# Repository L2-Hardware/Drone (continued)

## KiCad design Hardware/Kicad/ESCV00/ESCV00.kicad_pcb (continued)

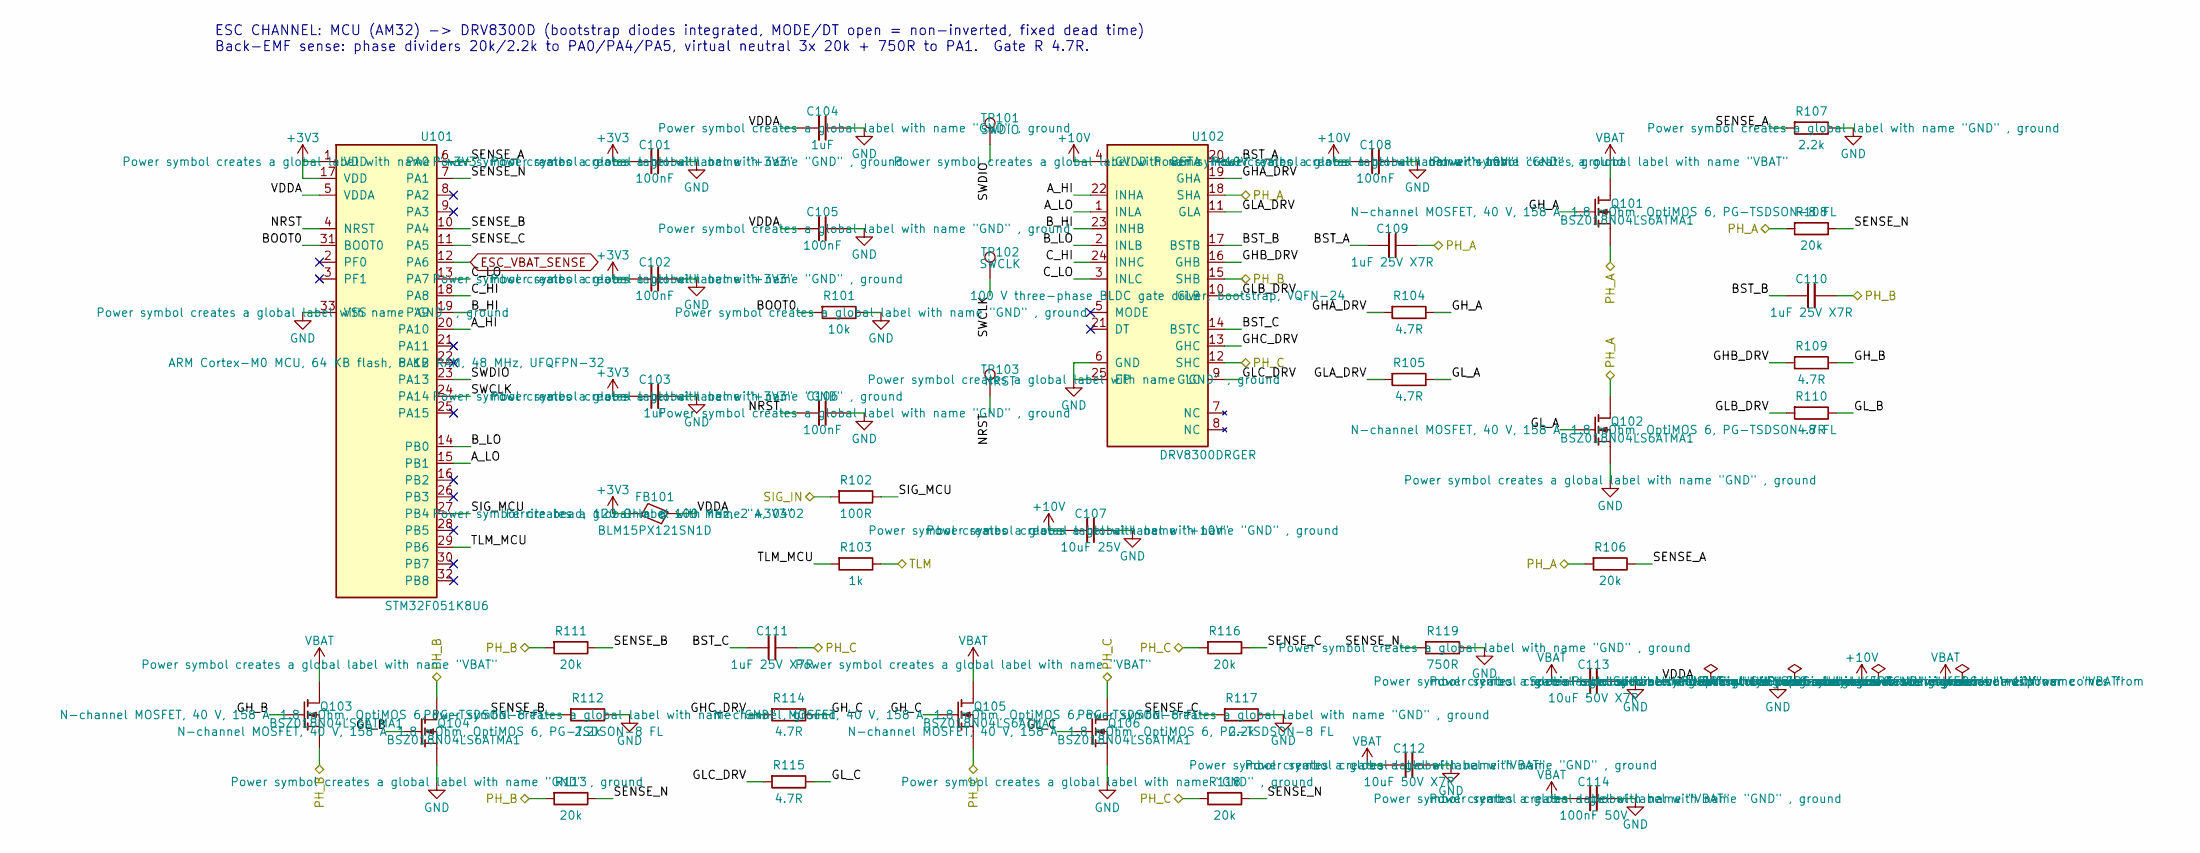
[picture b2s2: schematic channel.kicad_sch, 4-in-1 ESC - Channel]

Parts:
C101, C102, C105, C106, C108: 100nF; C_0402_1005Metric
C103, C104: 1uF; C_0402_1005Metric
C107: 10uF 25V; C_0805_2012Metric
C109, C110, C111: 1uF 25V X7R; C_0603_1608Metric
C112, C113: 10uF 50V X7R; C_1206_3216Metric
C114: 100nF 50V; C_0603_1608Metric
FB101: BLM15PX121SN1D
Q101, Q102, Q103, Q104, Q105, Q106: BSZ018N04LS6ATMA1
R101: 10k; R_0402_1005Metric
R102: 100R; R_0402_1005Metric
R103: 1k; R_0402_1005Metric
R104, R105, R109, R110, R114, R115: 4.7R; R_0402_1005Metric
R106, R108, R111, R113, R116, R118: 20k; R_0402_1005Metric
R107, R112, R117: 2.2k; R_0402_1005Metric
R119: 750R; R_0402_1005Metric
TP101: SWDIO; TestPoint_Pad_D1.0mm
TP102: SWCLK; TestPoint_Pad_D1.0mm
TP103: NRST; TestPoint_Pad_D1.0mm
U101: STM32F051K8U6
U102: DRV8300DRGER

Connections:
+3V3: C101.1, C102.1, C103.1, FB101.1, U101.1 (VDD), U101.17 (VDD); also elsewhere on the board
+10V: C107.1, C108.1, U102.4 (GVDD); also elsewhere on the board
/CH1/A_HI: U101.20 (PA10), U102.22 (INHA)
/CH1/A_LO: U101.15 (PB1), U102.1 (INLA)
/CH1/BOOT0: R101.1, U101.31 (BOOT0)
/CH1/BST_A: C109.1, U102.20 (BSTA)
/CH1/BST_B: C110.1, U102.17 (BSTB)
/CH1/BST_C: C111.1, U102.14 (BSTC)
/CH1/B_HI: U101.19 (PA9), U102.23 (INHB)
/CH1/B_LO: U101.14 (PB0), U102.2 (INLB)
/CH1/C_HI: U101.18 (PA8), U102.24 (INHC)
/CH1/C_LO: U101.13 (PA7), U102.3 (INLC)
/CH1/GHA_DRV: R104.1, U102.19 (GHA)
/CH1/GHB_DRV: R109.1, U102.16 (GHB)
/CH1/GHC_DRV: R114.1, U102.13 (GHC)
/CH1/GH_A: Q101.4 (G), R104.2
/CH1/GH_B: Q103.4 (G), R109.2
/CH1/GH_C: Q105.4 (G), R114.2
/CH1/GLA_DRV: R105.1, U102.11 (GLA)
/CH1/GLB_DRV: R110.1, U102.10 (GLB)
/CH1/GLC_DRV: R115.1, U102.9 (GLC)
/CH1/GL_A: Q102.4 (G), R105.2
/CH1/GL_B: Q104.4 (G), R110.2
/CH1/GL_C: Q106.4 (G), R115.2
/CH1/NRST: C106.1, TP103.1, U101.4 (NRST)
/CH1/SENSE_A: R106.2, R107.1, U101.6 (PA0)
/CH1/SENSE_B: R111.2, R112.1, U101.10 (PA4)
/CH1/SENSE_C: R116.2, R117.1, U101.11 (PA5)
/CH1/SENSE_N: R108.2, R113.2, R118.2, R119.1, U101.7 (PA1)
/CH1/SIG_MCU: R102.2, U101.27 (PB4)
/CH1/SWCLK: TP102.1, U101.24 (PA14)
/CH1/SWDIO: TP101.1, U101.23 (PA13)
/CH1/TLM_MCU: R103.1, U101.29 (PB6)
/CH1/VDDA: C104.1, C105.1, FB101.2, U101.5 (VDDA)
ESC_TLM: R103.2; also elsewhere on the board
ESC_VBAT_SENSE: U101.12 (PA6); also elsewhere on the board
GND: C101.2, C102.2, C103.2, C104.2, C105.2, C106.2, C107.2, C108.2, C112.2, C113.2, C114.2, Q102.1 (S), Q102.2 (S), Q102.3 (S), Q104.1 (S), Q104.2 (S), Q104.3 (S), Q106.1 (S), Q106.2 (S), Q106.3 (S), R101.2, R107.2, R112.2, R117.2, R119.2, U101.33 (VSS), U102.6 (GND), U102.25 (EP); also elsewhere on the board
M1_A: C109.2, Q101.1 (S), Q101.2 (S), Q101.3 (S), Q102.5 (D), R106.1, R108.1, U102.18 (SHA); also elsewhere on the board
M1_B: C110.2, Q103.1 (S), Q103.2 (S), Q103.3 (S), Q104.5 (D), R111.1, R113.1, U102.15 (SHB); also elsewhere on the board
M1_C: C111.2, Q105.1 (S), Q105.2 (S), Q105.3 (S), Q106.5 (D), R116.1, R118.1, U102.12 (SHC); also elsewhere on the board
MOTOR1: R102.1; also elsewhere on the board
VBAT: C112.1, C113.1, C114.1, Q101.5 (D), Q103.5 (D), Q105.5 (D); also elsewhere on the board

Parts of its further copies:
C201, C202, C205, C206, C208, C301, C302, C305, C306, C308, C401, C402, C405, C406, C408: 100nF; C_0402_1005Metric
C203, C204, C303, C304, C403, C404: 1uF; C_0402_1005Metric
C207, C307, C407: 10uF 25V; C_0805_2012Metric
C209, C210, C211, C309, C310, C311, C409, C410, C411: 1uF 25V X7R; C_0603_1608Metric
C212, C213, C312, C313, C412, C413: 10uF 50V X7R; C_1206_3216Metric
C214, C314, C414: 100nF 50V; C_0603_1608Metric
FB201, FB301, FB401: BLM15PX121SN1D
Q201, Q202, Q203, Q204, Q205, Q206, Q301, Q302, Q303, Q304, Q305, Q306, Q401, Q402, Q403, Q404, Q405, Q406: BSZ018N04LS6ATMA1
R201, R301, R401: 10k; R_0402_1005Metric
R202, R302, R402: 100R; R_0402_1005Metric
R203, R303, R403: 1k; R_0402_1005Metric
R204, R205, R209, R210, R214, R215, R304, R305, R309, R310, R314, R315, R404, R405, R409, R410, R414, R415: 4.7R; R_0402_1005Metric
R206, R208, R211, R213, R216, R218, R306, R308, R311, R313, R316, R318, R406, R408, R411, R413, R416, R418: 20k; R_0402_1005Metric
R207, R212, R217, R307, R312, R317, R407, R412, R417: 2.2k; R_0402_1005Metric
R219, R319, R419: 750R; R_0402_1005Metric
TP201, TP301, TP401: SWDIO; TestPoint_Pad_D1.0mm
TP202, TP302, TP402: SWCLK; TestPoint_Pad_D1.0mm
TP203, TP303, TP403: NRST; TestPoint_Pad_D1.0mm
U201, U301, U401: STM32F051K8U6
U202, U302, U402: DRV8300DRGER

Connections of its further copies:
+3V3: C201.1, C202.1, C203.1, C301.1, C302.1, C303.1, C401.1, C402.1, C403.1, FB201.1, FB301.1, FB401.1, U201.1 (VDD), U201.17 (VDD), U301.1 (VDD), U301.17 (VDD), U401.1 (VDD), U401.17 (VDD); also elsewhere on the board
+10V: C207.1, C208.1, C307.1, C308.1, C407.1, C408.1, U202.4 (GVDD), U302.4 (GVDD), U402.4 (GVDD); also elsewhere on the board
/CH2/A_HI: U201.20 (PA10), U202.22 (INHA)
/CH2/A_LO: U201.15 (PB1), U202.1 (INLA)
/CH2/BOOT0: R201.1, U201.31 (BOOT0)
/CH2/BST_A: C209.1, U202.20 (BSTA)
/CH2/BST_B: C210.1, U202.17 (BSTB)
/CH2/BST_C: C211.1, U202.14 (BSTC)
/CH2/B_HI: U201.19 (PA9), U202.23 (INHB)
/CH2/B_LO: U201.14 (PB0), U202.2 (INLB)
/CH2/C_HI: U201.18 (PA8), U202.24 (INHC)
/CH2/C_LO: U201.13 (PA7), U202.3 (INLC)
/CH2/GHA_DRV: R204.1, U202.19 (GHA)
/CH2/GHB_DRV: R209.1, U202.16 (GHB)
/CH2/GHC_DRV: R214.1, U202.13 (GHC)
/CH2/GH_A: Q201.4 (G), R204.2
/CH2/GH_B: Q203.4 (G), R209.2
/CH2/GH_C: Q205.4 (G), R214.2
/CH2/GLA_DRV: R205.1, U202.11 (GLA)
/CH2/GLB_DRV: R210.1, U202.10 (GLB)
/CH2/GLC_DRV: R215.1, U202.9 (GLC)
/CH2/GL_A: Q202.4 (G), R205.2
/CH2/GL_B: Q204.4 (G), R210.2
/CH2/GL_C: Q206.4 (G), R215.2
/CH2/NRST: C206.1, TP203.1, U201.4 (NRST)
/CH2/SENSE_A: R206.2, R207.1, U201.6 (PA0)
/CH2/SENSE_B: R211.2, R212.1, U201.10 (PA4)
/CH2/SENSE_C: R216.2, R217.1, U201.11 (PA5)
/CH2/SENSE_N: R208.2, R213.2, R218.2, R219.1, U201.7 (PA1)
/CH2/SIG_MCU: R202.2, U201.27 (PB4)
/CH2/SWCLK: TP202.1, U201.24 (PA14)
/CH2/SWDIO: TP201.1, U201.23 (PA13)
/CH2/TLM_MCU: R203.1, U201.29 (PB6)
/CH2/VDDA: C204.1, C205.1, FB201.2, U201.5 (VDDA)
/CH3/A_HI: U301.20 (PA10), U302.22 (INHA)
/CH3/A_LO: U301.15 (PB1), U302.1 (INLA)
/CH3/BOOT0: R301.1, U301.31 (BOOT0)
/CH3/BST_A: C309.1, U302.20 (BSTA)
/CH3/BST_B: C310.1, U302.17 (BSTB)
/CH3/BST_C: C311.1, U302.14 (BSTC)
/CH3/B_HI: U301.19 (PA9), U302.23 (INHB)
/CH3/B_LO: U301.14 (PB0), U302.2 (INLB)
/CH3/C_HI: U301.18 (PA8), U302.24 (INHC)
/CH3/C_LO: U301.13 (PA7), U302.3 (INLC)
/CH3/GHA_DRV: R304.1, U302.19 (GHA)
/CH3/GHB_DRV: R309.1, U302.16 (GHB)
/CH3/GHC_DRV: R314.1, U302.13 (GHC)
/CH3/GH_A: Q301.4 (G), R304.2
/CH3/GH_B: Q303.4 (G), R309.2
/CH3/GH_C: Q305.4 (G), R314.2
/CH3/GLA_DRV: R305.1, U302.11 (GLA)
/CH3/GLB_DRV: R310.1, U302.10 (GLB)
/CH3/GLC_DRV: R315.1, U302.9 (GLC)
/CH3/GL_A: Q302.4 (G), R305.2
/CH3/GL_B: Q304.4 (G), R310.2
/CH3/GL_C: Q306.4 (G), R315.2
/CH3/NRST: C306.1, TP303.1, U301.4 (NRST)
/CH3/SENSE_A: R306.2, R307.1, U301.6 (PA0)
/CH3/SENSE_B: R311.2, R312.1, U301.10 (PA4)
/CH3/SENSE_C: R316.2, R317.1, U301.11 (PA5)
/CH3/SENSE_N: R308.2, R313.2, R318.2, R319.1, U301.7 (PA1)
/CH3/SIG_MCU: R302.2, U301.27 (PB4)
/CH3/SWCLK: TP302.1, U301.24 (PA14)
/CH3/SWDIO: TP301.1, U301.23 (PA13)
/CH3/TLM_MCU: R303.1, U301.29 (PB6)
/CH3/VDDA: C304.1, C305.1, FB301.2, U301.5 (VDDA)
/CH4/A_HI: U401.20 (PA10), U402.22 (INHA)
/CH4/A_LO: U401.15 (PB1), U402.1 (INLA)
/CH4/BOOT0: R401.1, U401.31 (BOOT0)
/CH4/BST_A: C409.1, U402.20 (BSTA)
/CH4/BST_B: C410.1, U402.17 (BSTB)
/CH4/BST_C: C411.1, U402.14 (BSTC)
/CH4/B_HI: U401.19 (PA9), U402.23 (INHB)
/CH4/B_LO: U401.14 (PB0), U402.2 (INLB)
/CH4/C_HI: U401.18 (PA8), U402.24 (INHC)
/CH4/C_LO: U401.13 (PA7), U402.3 (INLC)
/CH4/GHA_DRV: R404.1, U402.19 (GHA)
/CH4/GHB_DRV: R409.1, U402.16 (GHB)
/CH4/GHC_DRV: R414.1, U402.13 (GHC)
/CH4/GH_A: Q401.4 (G), R404.2
/CH4/GH_B: Q403.4 (G), R409.2
/CH4/GH_C: Q405.4 (G), R414.2
/CH4/GLA_DRV: R405.1, U402.11 (GLA)
/CH4/GLB_DRV: R410.1, U402.10 (GLB)
/CH4/GLC_DRV: R415.1, U402.9 (GLC)
/CH4/GL_A: Q402.4 (G), R405.2
/CH4/GL_B: Q404.4 (G), R410.2
/CH4/GL_C: Q406.4 (G), R415.2
/CH4/NRST: C406.1, TP403.1, U401.4 (NRST)
/CH4/SENSE_A: R406.2, R407.1, U401.6 (PA0)
/CH4/SENSE_B: R411.2, R412.1, U401.10 (PA4)
/CH4/SENSE_C: R416.2, R417.1, U401.11 (PA5)
/CH4/SENSE_N: R408.2, R413.2, R418.2, R419.1, U401.7 (PA1)
/CH4/SIG_MCU: R402.2, U401.27 (PB4)
/CH4/SWCLK: TP402.1, U401.24 (PA14)
/CH4/SWDIO: TP401.1, U401.23 (PA13)
/CH4/TLM_MCU: R403.1, U401.29 (PB6)
/CH4/VDDA: C404.1, C405.1, FB401.2, U401.5 (VDDA)
ESC_TLM: R203.2, R303.2, R403.2; also elsewhere on the board
ESC_VBAT_SENSE: U201.12 (PA6), U301.12 (PA6), U401.12 (PA6); also elsewhere on the board
GND: C201.2, C202.2, C203.2, C204.2, C205.2, C206.2, C207.2, C208.2, C212.2, C213.2, C214.2, C301.2, C302.2, C303.2, C304.2, C305.2, C306.2, C307.2, C308.2, C312.2, C313.2, C314.2, C401.2, C402.2, C403.2, C404.2, C405.2, C406.2, C407.2, C408.2, C412.2, C413.2, C414.2, Q202.1 (S), Q202.2 (S), Q202.3 (S), Q204.1 (S), Q204.2 (S), Q204.3 (S), Q206.1 (S), Q206.2 (S), Q206.3 (S), Q302.1 (S), Q302.2 (S), Q302.3 (S), Q304.1 (S), Q304.2 (S), Q304.3 (S), Q306.1 (S), Q306.2 (S), Q306.3 (S), Q402.1 (S), Q402.2 (S), Q402.3 (S), Q404.1 (S), Q404.2 (S), Q404.3 (S), Q406.1 (S), Q406.2 (S), Q406.3 (S), R201.2, R207.2, R212.2, R217.2, R219.2, R301.2, R307.2, R312.2, R317.2, R319.2, R401.2, R407.2, R412.2, R417.2, R419.2, U201.33 (VSS), U202.6 (GND), U202.25 (EP), U301.33 (VSS), U302.6 (GND), U302.25 (EP), U401.33 (VSS), U402.6 (GND), U402.25 (EP); also elsewhere on the board
M2_A: C209.2, Q201.1 (S), Q201.2 (S), Q201.3 (S), Q202.5 (D), R206.1, R208.1, U202.18 (SHA); also elsewhere on the board
M2_B: C210.2, Q203.1 (S), Q203.2 (S), Q203.3 (S), Q204.5 (D), R211.1, R213.1, U202.15 (SHB); also elsewhere on the board
M2_C: C211.2, Q205.1 (S), Q205.2 (S), Q205.3 (S), Q206.5 (D), R216.1, R218.1, U202.12 (SHC); also elsewhere on the board
M3_A: C309.2, Q301.1 (S), Q301.2 (S), Q301.3 (S), Q302.5 (D), R306.1, R308.1, U302.18 (SHA); also elsewhere on the board
M3_B: C310.2, Q303.1 (S), Q303.2 (S), Q303.3 (S), Q304.5 (D), R311.1, R313.1, U302.15 (SHB); also elsewhere on the board
M3_C: C311.2, Q305.1 (S), Q305.2 (S), Q305.3 (S), Q306.5 (D), R316.1, R318.1, U302.12 (SHC); also elsewhere on the board
M4_A: C409.2, Q401.1 (S), Q401.2 (S), Q401.3 (S), Q402.5 (D), R406.1, R408.1, U402.18 (SHA); also elsewhere on the board
M4_B: C410.2, Q403.1 (S), Q403.2 (S), Q403.3 (S), Q404.5 (D), R411.1, R413.1, U402.15 (SHB); also elsewhere on the board
M4_C: C411.2, Q405.1 (S), Q405.2 (S), Q405.3 (S), Q406.5 (D), R416.1, R418.1, U402.12 (SHC); also elsewhere on the board
MOTOR2: R202.1; also elsewhere on the board
MOTOR3: R302.1; also elsewhere on the board
MOTOR4: R402.1; also elsewhere on the board
VBAT: C212.1, C213.1, C214.1, C312.1, C313.1, C314.1, C412.1, C413.1, C414.1, Q201.5 (D), Q203.5 (D), Q205.5 (D), Q301.5 (D), Q303.5 (D), Q305.5 (D), Q401.5 (D), Q403.5 (D), Q405.5 (D); also elsewhere on the board

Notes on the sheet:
ESC CHANNEL: MCU (AM32) -> DRV8300D (bootstrap diodes integrated, MODE/DT open = non-inverted, fixed dead time) Back-EMF sense: phase dividers 20k/2.2k to PA0/PA4/PA5, virtual neutral 3x 20k + 750R to PA1. Gate R 4.7R.

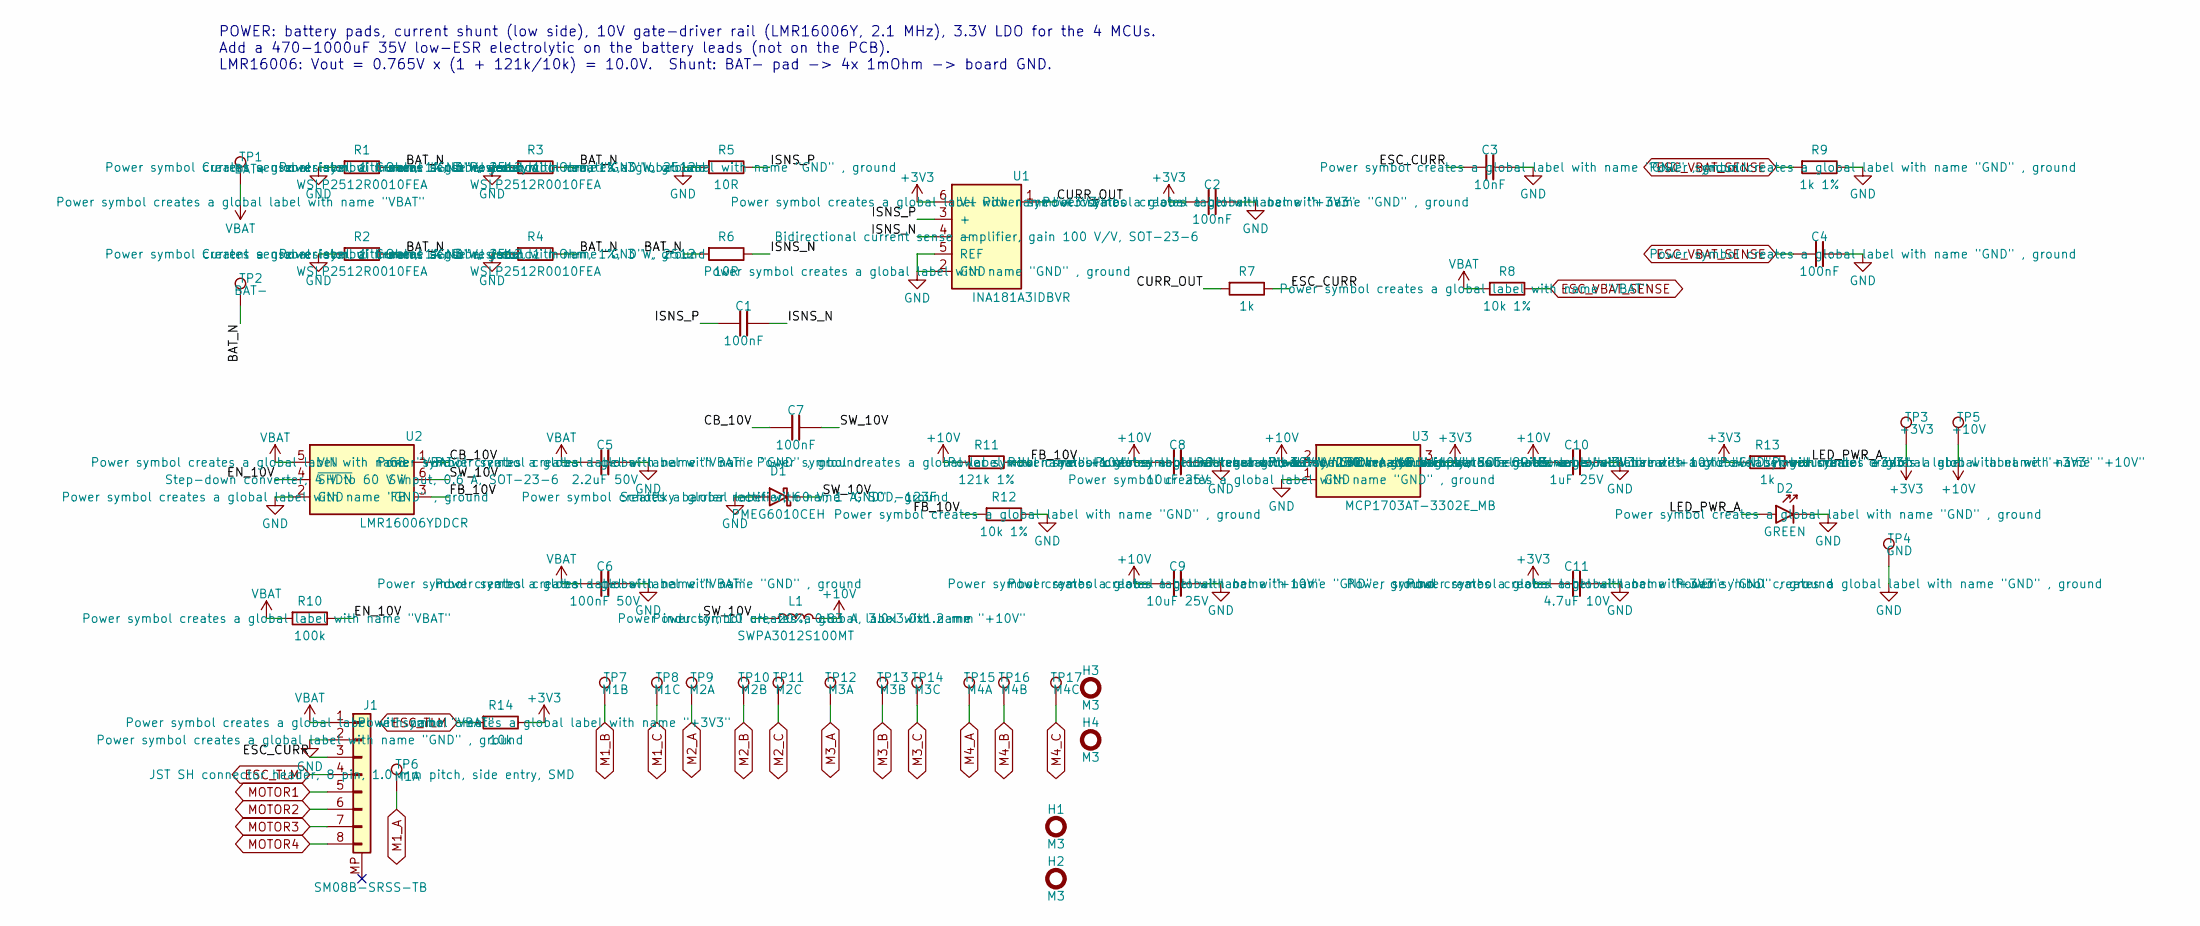
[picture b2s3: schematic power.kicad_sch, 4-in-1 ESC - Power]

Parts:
C1, C2, C4, C7: 100nF; C_0402_1005Metric
C3: 10nF; C_0402_1005Metric
C5: 2.2uF 50V; C_0805_2012Metric
C6: 100nF 50V; C_0603_1608Metric
C8, C9: 10uF 25V; C_0805_2012Metric
C10: 1uF 25V; C_0603_1608Metric
C11: 4.7uF 10V; C_0603_1608Metric
D1: PMEG6010CEH
D2: GREEN; LED_0603_1608Metric
H1, H2, H3, H4: M3; MountingHole_3.2mm_M3
J1: SM08B-SRSS-TB
L1: SWPA3012S100MT
R1, R2, R3, R4: WSLP2512R0010FEA
R5, R6: 10R; R_0402_1005Metric
R7, R13: 1k; R_0402_1005Metric
R8, R12: 10k 1%; R_0402_1005Metric
R9: 1k 1%; R_0402_1005Metric
R10: 100k; R_0402_1005Metric
R11: 121k 1%; R_0402_1005Metric
R14: 10k; R_0402_1005Metric
TP1: BAT+; SolderPad_5x8mm
TP2: BAT-; SolderPad_5x8mm
TP3: +3V3; TestPoint_Pad_D1.5mm
TP4: GND; TestPoint_Pad_D1.5mm
TP5: +10V; TestPoint_Pad_D1.5mm
TP6: M1A; SolderPad_3x5mm
TP7: M1B; SolderPad_3x5mm
TP8: M1C; SolderPad_3x5mm
TP9: M2A; SolderPad_3x5mm
TP10: M2B; SolderPad_3x5mm
TP11: M2C; SolderPad_3x5mm
TP12: M3A; SolderPad_3x5mm
TP13: M3B; SolderPad_3x5mm
TP14: M3C; SolderPad_3x5mm
TP15: M4A; SolderPad_3x5mm
TP16: M4B; SolderPad_3x5mm
TP17: M4C; SolderPad_3x5mm
U1: INA181A3IDBVR
U2: LMR16006YDDCR
U3: MCP1703AT-3302E_MB

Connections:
+3V3: C2.1, C11.1, R13.1, R14.2, TP3.1, U1.6 (V+), U3.3 (VO); also elsewhere on the board
+10V: C8.1, C9.1, C10.1, L1.2, R11.1, TP5.1, U3.2 (VI); also elsewhere on the board
/Power/BAT_N: R1.2, R2.2, R3.2, R4.2, R6.1, TP2.1
/Power/CB_10V: C7.1, U2.1 (CB)
/Power/CURR_OUT: R7.1, U1.1
/Power/EN_10V: R10.2, U2.4 (~SHDN)
/Power/ESC_CURR: C3.1, J1.3, R7.2
/Power/FB_10V: R11.2, R12.1, U2.3 (FB)
/Power/ISNS_N: C1.2, R6.2, U1.4 (-)
/Power/ISNS_P: C1.1, R5.2, U1.3 (+)
/Power/LED_PWR_A: D2.2 (A), R13.2
/Power/SW_10V: C7.2, D1.1 (K), L1.1, U2.6 (SW)
ESC_TLM: J1.4, R14.1; also elsewhere on the board
ESC_VBAT_SENSE: C4.1, R8.2, R9.1; also elsewhere on the board
GND: C2.2, C3.2, C4.2, C5.2, C6.2, C8.2, C9.2, C10.2, C11.2, D1.2 (A), D2.1 (K), J1.2, R1.1, R2.1, R3.1, R4.1, R5.1, R9.2, R12.2, TP4.1, U1.2 (GND), U1.5 (REF), U2.2 (GND), U3.1 (GND); also elsewhere on the board
M1_A: TP6.1; also elsewhere on the board
M1_B: TP7.1; also elsewhere on the board
M1_C: TP8.1; also elsewhere on the board
M2_A: TP9.1; also elsewhere on the board
M2_B: TP10.1; also elsewhere on the board
M2_C: TP11.1; also elsewhere on the board
M3_A: TP12.1; also elsewhere on the board
M3_B: TP13.1; also elsewhere on the board
M3_C: TP14.1; also elsewhere on the board
M4_A: TP15.1; also elsewhere on the board
M4_B: TP16.1; also elsewhere on the board
M4_C: TP17.1; also elsewhere on the board
MOTOR1: J1.5; also elsewhere on the board
MOTOR2: J1.6; also elsewhere on the board
MOTOR3: J1.7; also elsewhere on the board
MOTOR4: J1.8; also elsewhere on the board
VBAT: C5.1, C6.1, J1.1, R8.1, R10.1, TP1.1, U2.5 (VIN); also elsewhere on the board

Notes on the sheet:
POWER: battery pads, current shunt (low side), 10V gate-driver rail (LMR16006Y, 2.1 MHz), 3.3V LDO for the 4 MCUs. Add a 470-1000uF 35V low-ESR electrolytic on the battery leads (not on the PCB). LMR16006: Vout = 0.765V x (1 + 121k/10k) = 10.0V. Shunt: BAT- pad -> 4x 1mOhm -> board GND.

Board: 6 copper layers, 233 parts (0 on the bottom side), 160 nets, no tracks yet.

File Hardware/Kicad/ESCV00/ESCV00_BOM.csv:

"Qty","References","Value","Footprint","DNP"
"24","C1,C2,C4,C7,C101,C102,C105,C106,C108,C201,C202,C205,C206,C208,C301,C302,C305,C306,C308,C401,C402,C405,C406,C408","100nF","eCapacitor:C_0402_1005Metric",""
"1","C3","10nF","eCapacitor:C_0402_1005Metric",""
"1","C5","2.2uF 50V","eCapacitor:C_0805_2012Metric",""
"5","C6,C114,C214,C314,C414","100nF 50V","eCapacitor:C_0603_1608Metric",""
"6","C8,C9,C107,C207,C307,C407","10uF 25V","eCapacitor:C_0805_2012Metric",""
"1","C10","1uF 25V","eCapacitor:C_0603_1608Metric",""
"1","C11","4.7uF 10V","eCapacitor:C_0603_1608Metric",""
"8","C103,C104,C203,C204,C303,C304,C403,C404","1uF","eCapacitor:C_0402_1005Metric",""
"12","C109,C110,C111,C209,C210,C211,C309,C310,C311,C409,C410,C411","1uF 25V X7R","eCapacitor:C_0603_1608Metric",""
"8","C112,C113,C212,C213,C312,C313,C412,C413","10uF 50V X7R","eCapacitor:C_1206_3216Metric",""
"1","D1","PMEG6010CEH","eDiodes:PMEG6010CEH",""
"1","D2","GREEN","eLED:LED_0603_1608Metric",""
"4","FB101,FB201,FB301,FB401","BLM15PX121SN1D","eFerrite:BLM15PX121SN1D",""
"1","J1","SM08B-SRSS-TB","eConnector:SM08B-SRSS-TB",""
"1","L1","SWPA3012S100MT","eCoil:SWPA3012S100MT",""
"24","Q101,Q102,Q103,Q104,Q105,Q106,Q201,Q202,Q203,Q204,Q205,Q206,Q301,Q302,Q303,Q304,Q305,Q306,Q401,Q402,Q403,Q404,Q405,Q406","BSZ018N04LS6ATMA1","eTransistor:BSZ018N04LS6ATMA1",""
"4","R1,R2,R3,R4","WSLP2512R0010FEA","eResistor:WSLP2512R0010FEA",""
"2","R5,R6","10R","eResistor:R_0402_1005Metric",""
"6","R7,R13,R103,R203,R303,R403","1k","eResistor:R_0402_1005Metric",""
"2","R8,R12","10k 1%","eResistor:R_0402_1005Metric",""
"1","R9","1k 1%","eResistor:R_0402_1005Metric",""
"1","R10","100k","eResistor:R_0402_1005Metric",""
"1","R11","121k 1%","eResistor:R_0402_1005Metric",""
"5","R14,R101,R201,R301,R401","10k","eResistor:R_0402_1005Metric",""
"4","R102,R202,R302,R402","100R","eResistor:R_0402_1005Metric",""
"24","R104,R105,R109,R110,R114,R115,R204,R205,R209,R210,R214,R215,R304,R305,R309,R310,R314,R315,R404,R405,R409,R410,R414,R415","4.7R","eResistor:R_0402_1005Metric",""
"24","R106,R108,R111,R113,R116,R118,R206,R208,R211,R213,R216,R218,R306,R308,R311,R313,R316,R318,R406,R408,R411,R413,R416,R418","20k","eResistor:R_0402_1005Metric",""
"12","R107,R112,R117,R207,R212,R217,R307,R312,R317,R407,R412,R417","2.2k","eResistor:R_0402_1005Metric",""
"4","R119,R219,R319,R419","750R","eResistor:R_0402_1005Metric",""
"1","U1","INA181A3IDBVR","eAmplifier:INA181A3IDBVR",""
"1","U2","LMR16006YDDCR","eConverterDCDC:LMR16006YDDCR",""
"1","U3","MCP1703AT-3302E_MB","eLinearReg:MCP1703AT-3302E_MB",""
"4","U101,U201,U301,U401","STM32F051K8U6","eMCU:STM32F051K8U6",""
"4","U102,U202,U302,U402","DRV8300DRGER","eInterface:DRV8300DRGER",""

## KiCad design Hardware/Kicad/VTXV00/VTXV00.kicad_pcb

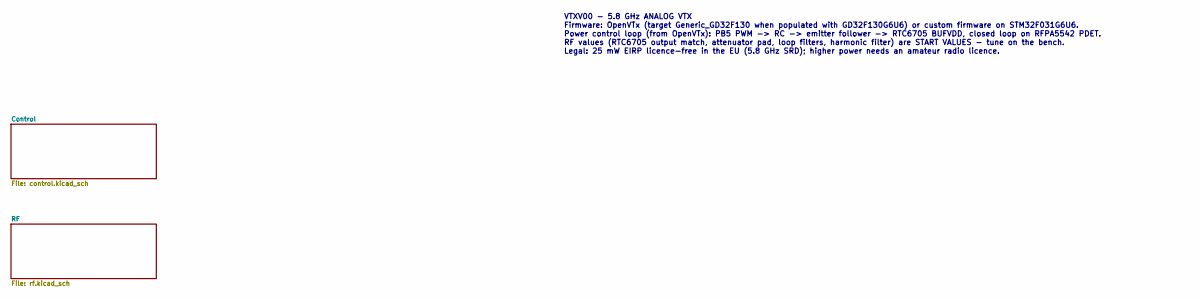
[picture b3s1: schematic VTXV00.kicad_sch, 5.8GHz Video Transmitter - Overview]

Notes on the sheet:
VTXV00 - 5.8 GHz ANALOG VTX Firmware: OpenVTx (target Generic_GD32F130 when populated with GD32F130G6U6) or custom firmware on STM32F031G6U6. Power control loop (from OpenVTx): PB5 PWM -> RC -> emitter follower -> RTC6705 BUFVDD, closed loop on RFPA5542 PDET. RF values (RTC6705 output match, attenu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

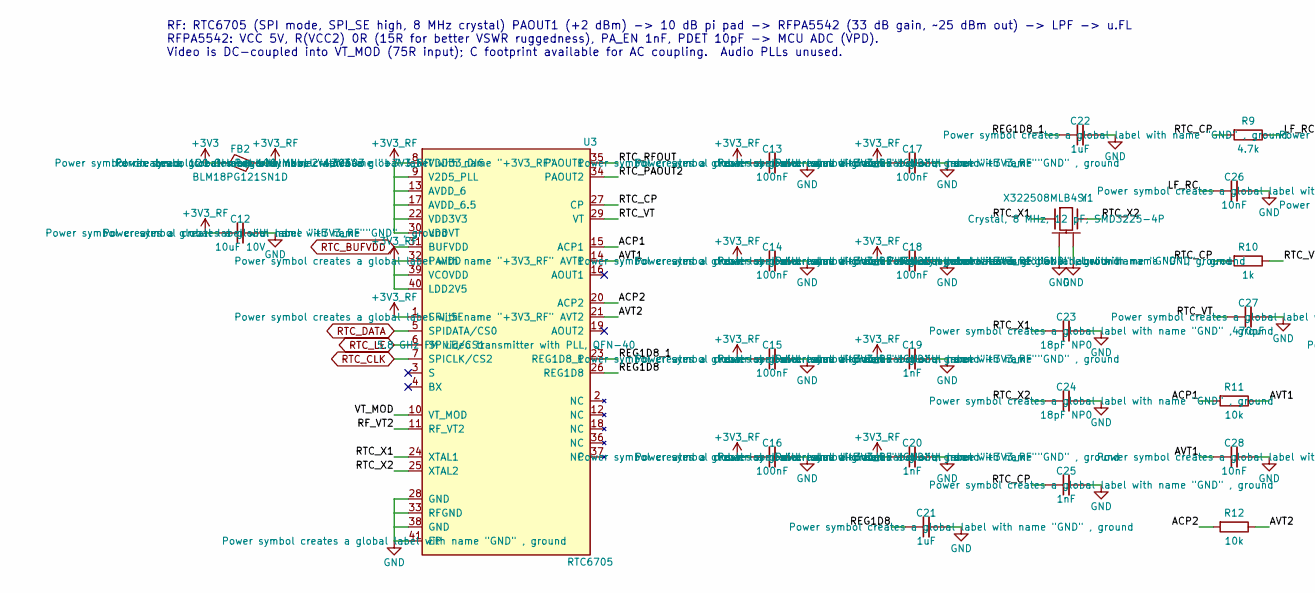
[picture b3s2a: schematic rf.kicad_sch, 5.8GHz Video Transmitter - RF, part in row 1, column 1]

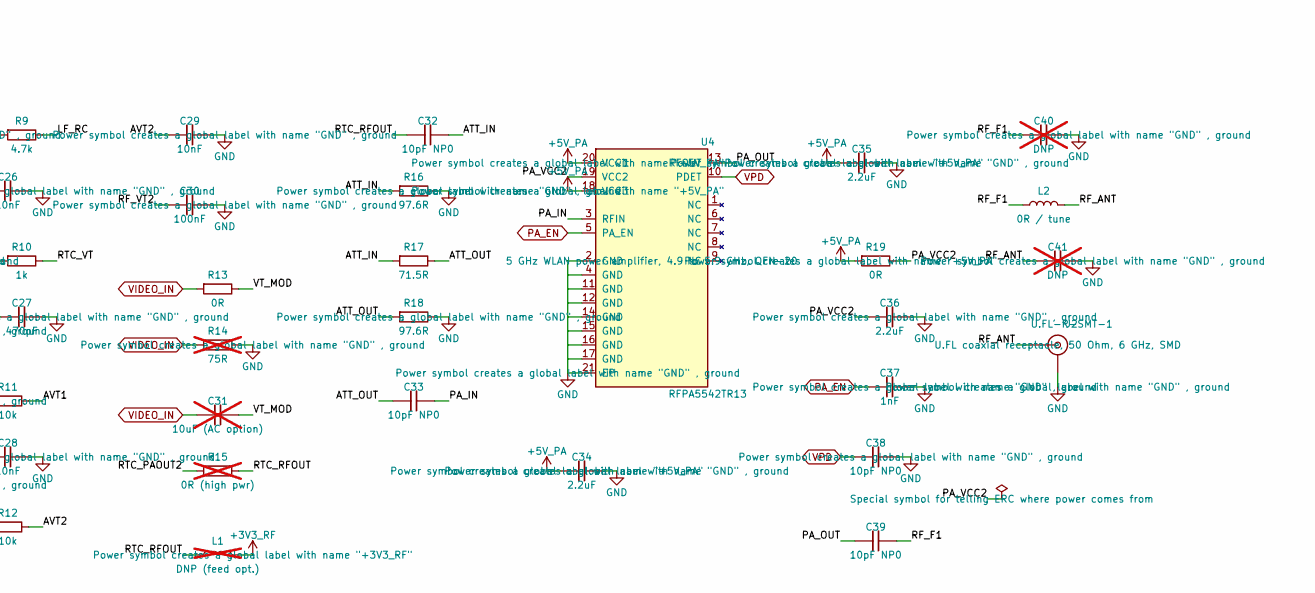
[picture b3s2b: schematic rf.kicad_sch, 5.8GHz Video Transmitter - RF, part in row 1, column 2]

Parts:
C12: 10uF 10V; C_0603_1608Metric
C13, C14, C15, C16, C17, C18, C30: 100nF; C_0402_1005Metric
C19, C20, C25, C37: 1nF; C_0402_1005Metric
C21, C22: 1uF; C_0402_1005Metric
C23, C24: 18pF NP0; C_0402_1005Metric
C26, C28, C29: 10nF; C_0402_1005Metric
C27: 470pF; C_0402_1005Metric
C31: 10uF (AC option); C_0603_1608Metric; not fitted
C32, C33, C38, C39: 10pF NP0; C_0402_1005Metric
C34, C35, C36: 2.2uF; C_0402_1005Metric
C40, C41: DNP; C_0402_1005Metric; not fitted
FB2: BLM18PG121SN1D
J2: U.FL-R-SMT-1
L1: DNP (feed opt.); L_0402_1005Metric; not fitted
L2: 0R / tune; L_0402_1005Metric
R9: 4.7k; R_0402_1005Metric
R10: 1k; R_0402_1005Metric
R11, R12: 10k; R_0402_1005Metric
R13, R19: 0R; R_0402_1005Metric
R14: 75R; R_0402_1005Metric; not fitted
R15: 0R (high pwr); R_0402_1005Metric; not fitted
R16, R18: 97.6R; R_0402_1005Metric
R17: 71.5R; R_0402_1005Metric
U3: RTC6705
U4: RFPA5542TR13
Y1: X322508MLB4SI

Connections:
+3V3: FB2.1; also elsewhere on the board
+3V3_RF: C12.1, C13.1, C14.1, C15.1, C16.1, C17.1, C18.1, C19.1, C20.1, FB2.2, L1.2, U3.1 (SPI_SE), U3.8 (VDD33_DIG), U3.9 (V2D5_PLL), U3.13 (AVDD_6), U3.17 (AVDD_6.5), U3.22 (VDD3V3), U3.30 (VDDVT), U3.32 (PAVDD), U3.39 (VCOVDD), U3.40 (LDD2V5); also elsewhere on the board
+5V_PA: C34.1, C35.1, R19.1, U4.18 (VCC3), U4.20 (VCC1); also elsewhere on the board
/RF/ACP1: R11.1, U3.15 (ACP1)
/RF/ACP2: R12.1, U3.20 (ACP2)
/RF/ATT_IN: C32.2, R16.1, R17.1
/RF/ATT_OUT: C33.1, R17.2, R18.1
/RF/AVT1: C28.1, R11.2, U3.14 (AVT1)
/RF/AVT2: C29.1, R12.2, U3.21 (AVT2)
/RF/LF_RC: C26.1, R9.2
/RF/PA_IN: C33.2, U4.3 (RFIN)
/RF/PA_OUT: C39.1, U4.13 (RFOUT)
/RF/PA_VCC2: C36.1, R19.2, U4.19 (VCC2)
/RF/REG1D8: C21.1, U3.26 (REG1D8)
/RF/REG1D8_1: C22.1, U3.23 (REG1D8_1)
/RF/RF_ANT: C41.1, J2.1 (In), L2.2
/RF/RF_F1: C39.2, C40.1, L2.1
/RF/RF_VT2: C30.1, U3.11 (RF_VT2)
/RF/RTC_CP: C25.1, R9.1, R10.1, U3.27 (CP)
/RF/RTC_PAOUT2: R15.1, U3.34 (PAOUT2)
/RF/RTC_RFOUT: C32.1, L1.1, R15.2, U3.35 (PAOUT1)
/RF/RTC_VT: C27.1, R10.2, U3.29 (VT)
/RF/RTC_X1: C23.1, U3.24 (XTAL1), Y1.1
/RF/RTC_X2: C24.1, U3.25 (XTAL2), Y1.3
/RF/VT_MOD: C31.2, R13.2, U3.10 (VT_MOD)
GND: C12.2, C13.2, C14.2, C15.2, C16.2, C17.2, C18.2, C19.2, C20.2, C21.2, C22.2, C23.2, C24.2, C25.2, C26.2, C27.2, C28.2, C29.2, C30.2, C34.2, C35.2, C36.2, C37.2, C38.2, C40.2, C41.2, J2.2 (Ext), R14.2, R16.2, R18.2, U3.28 (GND), U3.33 (RFGND), U3.38 (GND), U3.41 (EP), U4.2 (GND), U4.4 (GND), U4.11 (GND), U4.12 (GND), U4.14 (GND), U4.15 (GND), U4.16 (GND), U4.17 (GND), U4.21 (EP), Y1.2 (GND), Y1.4 (GND); also elsewhere on the board
PA_EN: C37.1, U4.5 (PA_EN); also elsewhere on the board
RTC_BUFVDD: U3.31 (BUFVDD); also elsewhere on the board
RTC_CLK: U3.7 (SPICLK/CS2); also elsewhere on the board
RTC_DATA: U3.5 (SPIDATA/CS0); also elsewhere on the board
RTC_LE: U3.6 (SPILE/CS1); also elsewhere on the board
VIDEO_IN: C31.1, R13.1, R14.1; also elsewhere on the board
VPD: C38.1, U4.10 (PDET); also elsewhere on the board

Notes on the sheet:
RF: RTC6705 (SPI mode, SPI_SE high, 8 MHz crystal) PAOUT1 (+2 dBm) -> 10 dB pi pad -> RFPA5542 (33 dB gain, ~25 dBm out) -> LPF -> u.FL RFPA5542: VCC 5V, R(VCC2) 0R (15R for better VSWR ruggedness), PA_EN 1nF, PDET 10pF -> MCU ADC (VPD). Video is DC-coupled into VT_MOD (75R input); C footprint avai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

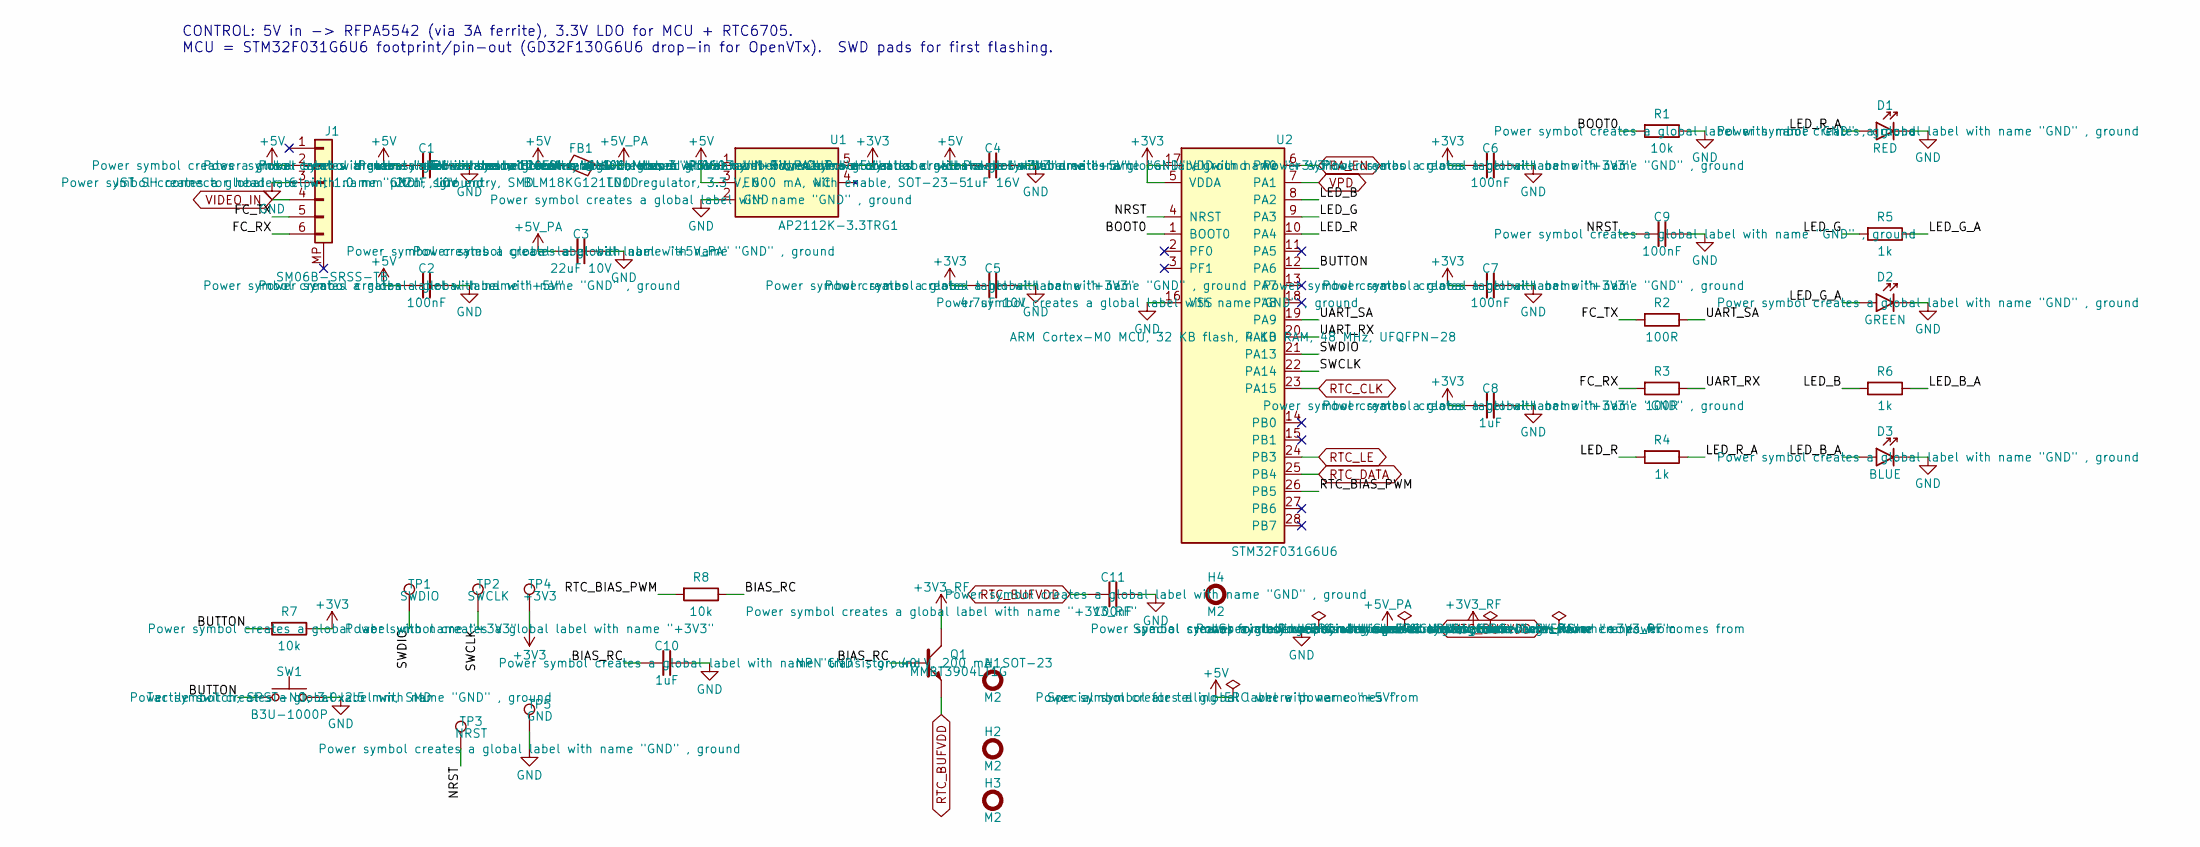
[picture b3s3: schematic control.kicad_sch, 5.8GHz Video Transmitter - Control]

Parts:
C1, C3: 22uF 10V; C_0805_2012Metric
C2, C6, C7, C9, C11: 100nF; C_0402_1005Metric
C4: 1uF 16V; C_0402_1005Metric
C5: 4.7uF 10V; C_0603_1608Metric
C8, C10: 1uF; C_0402_1005Metric
D1: RED; LED_0603_1608Metric
D2: GREEN; LED_0603_1608Metric
D3: BLUE; LED_0603_1608Metric
FB1: BLM18KG121TN1D
H1, H2, H3, H4: M2; MountingHole_2.2mm_M2
J1: SM06B-SRSS-TB
Q1: MMBT3904LT1G
R1, R7, R8: 10k; R_0402_1005Metric
R2, R3: 100R; R_0402_1005Metric
R4, R5, R6: 1k; R_0402_1005Metric
SW1: B3U-1000P
TP1: SWDIO; TestPoint_Pad_D1.0mm
TP2: SWCLK; TestPoint_Pad_D1.0mm
TP3: NRST; TestPoint_Pad_D1.0mm
TP4: +3V3; TestPoint_Pad_D1.0mm
TP5: GND; TestPoint_Pad_D1.0mm
U1: AP2112K-3.3TRG1
U2: STM32F031G6U6

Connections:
+3V3: C5.1, C6.1, C7.1, C8.1, R7.2, TP4.1, U1.5 (VOUT), U2.5 (VDDA), U2.17 (VDD); also elsewhere on the board
+3V3_RF: Q1.3 (C); also elsewhere on the board
+5V: C1.1, C2.1, C4.1, FB1.1, J1.2, U1.1 (VIN), U1.3 (EN)
+5V_PA: C3.1, FB1.2; also elsewhere on the board
/Control/BIAS_RC: C10.1, Q1.1 (B), R8.2
/Control/BOOT0: R1.1, U2.1 (BOOT0)
/Control/BUTTON: R7.1, SW1.1, U2.12 (PA6)
/Control/FC_RX: J1.6, R3.1
/Control/FC_TX: J1.5, R2.1
/Control/LED_B: R6.1, U2.8 (PA2)
/Control/LED_B_A: D3.2 (A), R6.2
/Control/LED_G: R5.1, U2.9 (PA3)
/Control/LED_G_A: D2.2 (A), R5.2
/Control/LED_R: R4.1, U2.10 (PA4)
/Control/LED_R_A: D1.2 (A), R4.2
/Control/NRST: C9.1, TP3.1, U2.4 (NRST)
/Control/RTC_BIAS_PWM: R8.1, U2.26 (PB5)
/Control/SWCLK: TP2.1, U2.22 (PA14)
/Control/SWDIO: TP1.1, U2.21 (PA13)
/Control/UART_RX: R3.2, U2.20 (PA10)
/Control/UART_SA: R2.2, U2.19 (PA9)
GND: C1.2, C2.2, C3.2, C4.2, C5.2, C6.2, C7.2, C8.2, C9.2, C10.2, C11.2, D1.1 (K), D2.1 (K), D3.1 (K), J1.3, R1.2, SW1.2, TP5.1, U1.2 (GND), U2.16 (VSS); also elsewhere on the board
PA_EN: U2.6 (PA0); also elsewhere on the board
RTC_BUFVDD: C11.1, Q1.2 (E); also elsewhere on the board
RTC_CLK: U2.23 (PA15); also elsewhere on the board
RTC_DATA: U2.25 (PB4); also elsewhere on the board
RTC_LE: U2.24 (PB3); also elsewhere on the board
VIDEO_IN: J1.4; also elsewhere on the board
VPD: U2.7 (PA1); also elsewhere on the board

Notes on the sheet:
CONTROL: 5V in -> RFPA5542 (via 3A ferrite), 3.3V LDO for MCU + RTC6705. MCU = STM32F031G6U6 footprint/pin-out (GD32F130G6U6 drop-in for OpenVTx). SWD pads for first flashing.

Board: 4 copper layers, 85 parts (0 on the bottom side), 51 nets, no tracks yet.

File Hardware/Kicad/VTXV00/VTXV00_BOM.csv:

"Qty","References","Value","Footprint","DNP"
"2","C1,C3","22uF 10V","eCapacitor:C_0805_2012Metric",""
"12","C2,C6,C7,C9,C11,C13,C14,C15,C16,C17,C18,C30","100nF","eCapacitor:C_0402_1005Metric",""
"1","C4","1uF 16V","eCapacitor:C_0402_1005Metric",""
"1","C5","4.7uF 10V","eCapacitor:C_0603_1608Metric",""
"4","C8,C10,C21,C22","1uF","eCapacitor:C_0402_1005Metric",""
"1","C12","10uF 10V","eCapacitor:C_0603_1608Metric",""
"4","C19,C20,C25,C37","1nF","eCapacitor:C_0402_1005Metric",""
"2","C23,C24","18pF NP0","eCapacitor:C_0402_1005Metric",""
"3","C26,C28,C29","10nF","eCapacitor:C_0402_1005Metric",""
"1","C27","470pF","eCapacitor:C_0402_1005Metric",""
"1","C31","10uF (AC option)","eCapacitor:C_0603_1608Metric","DNP"
"4","C32,C33,C38,C39","10pF NP0","eCapacitor:C_0402_1005Metric",""
"3","C34,C35,C36","2.2uF","eCapacitor:C_0402_1005Metric",""
"2","C40,C41","DNP","eCapacitor:C_0402_1005Metric","DNP"
"1","D1","RED","eLED:LED_0603_1608Metric",""
"1","D2","GREEN","eLED:LED_0603_1608Metric",""
"1","D3","BLUE","eLED:LED_0603_1608Metric",""
"1","FB1","BLM18KG121TN1D","eFerrite:BLM18KG121TN1D",""
"1","FB2","BLM18PG121SN1D","eFerrite:BLM18PG121SN1D",""
"1","J1","SM06B-SRSS-TB","eConnector:SM06B-SRSS-TB",""
"1","J2","U.FL-R-SMT-1","eConnector:U.FL-R-SMT-1",""
"1","L1","DNP (feed opt.)","eCoil:L_0402_1005Metric","DNP"
"1","L2","0R / tune","eCoil:L_0402_1005Metric",""
"1","Q1","MMBT3904LT1G","eTransistor:MMBT3904LT1G",""
"5","R1,R7,R8,R11,R12","10k","eResistor:R_0402_1005Metric",""
"2","R2,R3","100R","eResistor:R_0402_1005Metric",""
"4","R4,R5,R6,R10","1k","eResistor:R_0402_1005Metric",""
"1","R9","4.7k","eResistor:R_0402_1005Metric",""
"2","R13,R19","0R","eResistor:R_0402_1005Metric",""
"1","R14","75R","eResistor:R_0402_1005Metric","DNP"
"1","R15","0R (high pwr)","eResistor:R_0402_1005Metric","DNP"
"2","R16,R18","97.6R","eResistor:R_0402_1005Metric",""
"1","R17","71.5R","eResistor:R_0402_1005Metric",""
"1","SW1","B3U-1000P","eSwitch:B3U-1000P",""
"1","U1","AP2112K-3.3TRG1","eLinearReg:AP2112K-3.3TRG1",""
"1","U2","STM32F031G6U6","eMCU:STM32F031G6U6",""
"1","U3","RTC6705","eRFModule:RTC6705",""
"1","U4","RFPA5542TR13","eAmplifier:RFPA5542TR13",""
"1","Y1","X322508MLB4SI","eCrystal:X322508MLB4SI",""
